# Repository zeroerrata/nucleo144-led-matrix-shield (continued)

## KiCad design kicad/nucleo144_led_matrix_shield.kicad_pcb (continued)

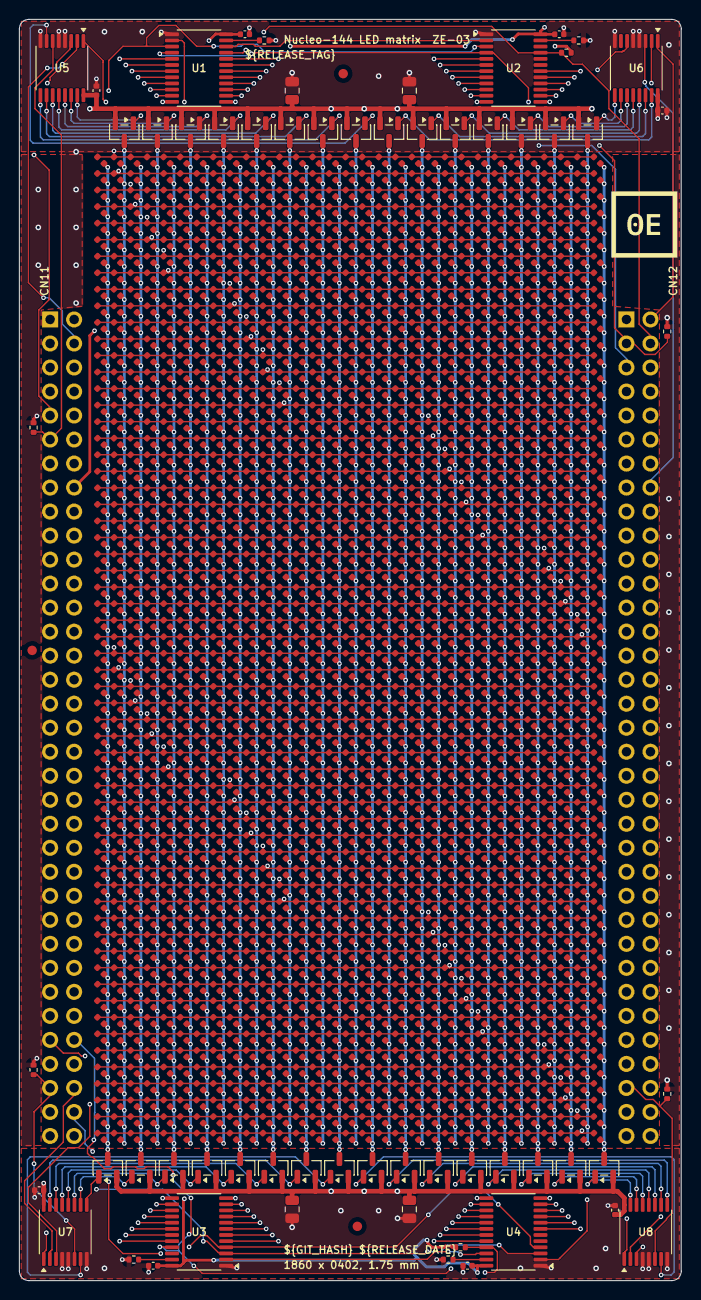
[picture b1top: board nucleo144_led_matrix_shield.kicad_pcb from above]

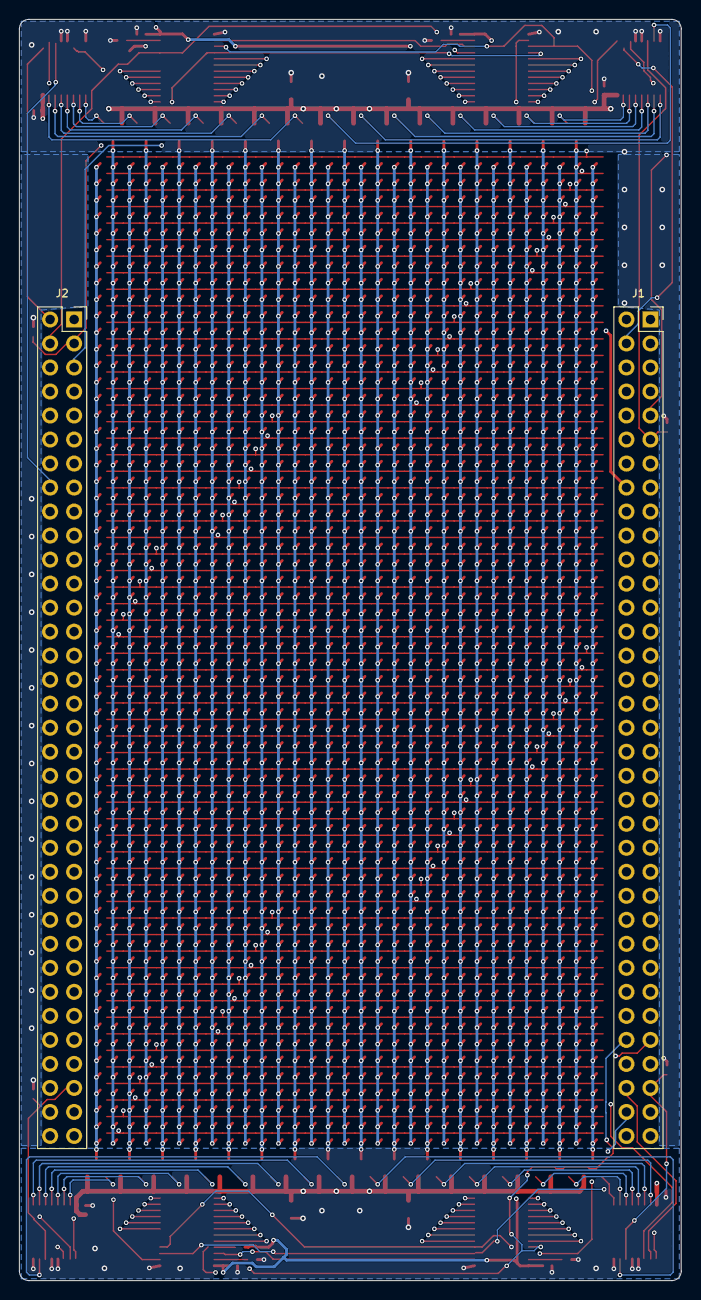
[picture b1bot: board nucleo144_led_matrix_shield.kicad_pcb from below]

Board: 4 copper layers, 70.0 x 133.4 mm, 1927 parts (2 on the bottom side), 155 nets.

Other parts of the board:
LOGO1: ZeroErrata logo; ZeroErrata_mark_7mm

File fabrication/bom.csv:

"Designator","Value","Footprint","Quantity","Manufacturer","MPN","LCSC Part #"
"C1-C8","100n","Capacitor_SMD:C_0402_1005Metric","8","Samsung","CL05B104KO5NNNC","C1525"
"C9-C12","22u 25V","Capacitor_SMD:C_0805_2012Metric","4","Samsung","CL21A226MAYNNNE","C602037"
"D101-D160,D201-D260,D301-D360,D401-D460,D501-D560,D601-D660,D701-D760,D801-D860,D901-D960,D1001-D1060,D1101-D1160,D1201-D1260,D1301-D1360,D1401-D1460,D1501-D1560,D1601-D1660,D1701-D1760,D1801-D1860,D1901-D1960,D2001-D2060,D2101-D2160,D2201-D2260,D2301-D2360,D2401-D2460,D2501-D2560,D2601-D2660,D2701-D2760,D2801-D2860,D2901-D2960,D3001-D3060,D3101-D3160","red","led_matrix:LED_0402_1005Metric_NoSilk","1860","Foshan NationStar","NCD0402R1","C130719"
"J1","CN11 Morpho socket","led_matrix:Morpho_2x35_P2.54mm_Socket_NoInnerAnnulus","1","Samtec","SSQ-135-01-T-D","C7088697"
"J2","CN12 Morpho socket","led_matrix:Morpho_2x35_P2.54mm_Socket_NoInnerAnnulus","1","Samtec","SSQ-135-01-T-D","C7088697"
"Q1-Q31","AO3401A","Package_TO_SOT_SMD:SOT-23","31","Alpha & Omega Semiconductor","AO3401A","C15127"
"R1-R4","3.3k","Resistor_SMD:R_0402_1005Metric","4","UNI-ROYAL","0402WGF3301TCE","C25890"
"R5-R10","10k","Resistor_SMD:R_0402_1005Metric","6","UNI-ROYAL","0402WGF1002TCE","C25744"
"U1-U4","STP16CP05TTR","Package_SO:TSSOP-24_4.4x7.8mm_P0.65mm","4","STMicroelectronics","STP16CP05TTR","C127267"
"U5-U8","74AHCT138","Package_SO:TSSOP-16_4.4x5mm_P0.65mm","4","Texas Instruments","SN74AHCT138PWR","C8205"
